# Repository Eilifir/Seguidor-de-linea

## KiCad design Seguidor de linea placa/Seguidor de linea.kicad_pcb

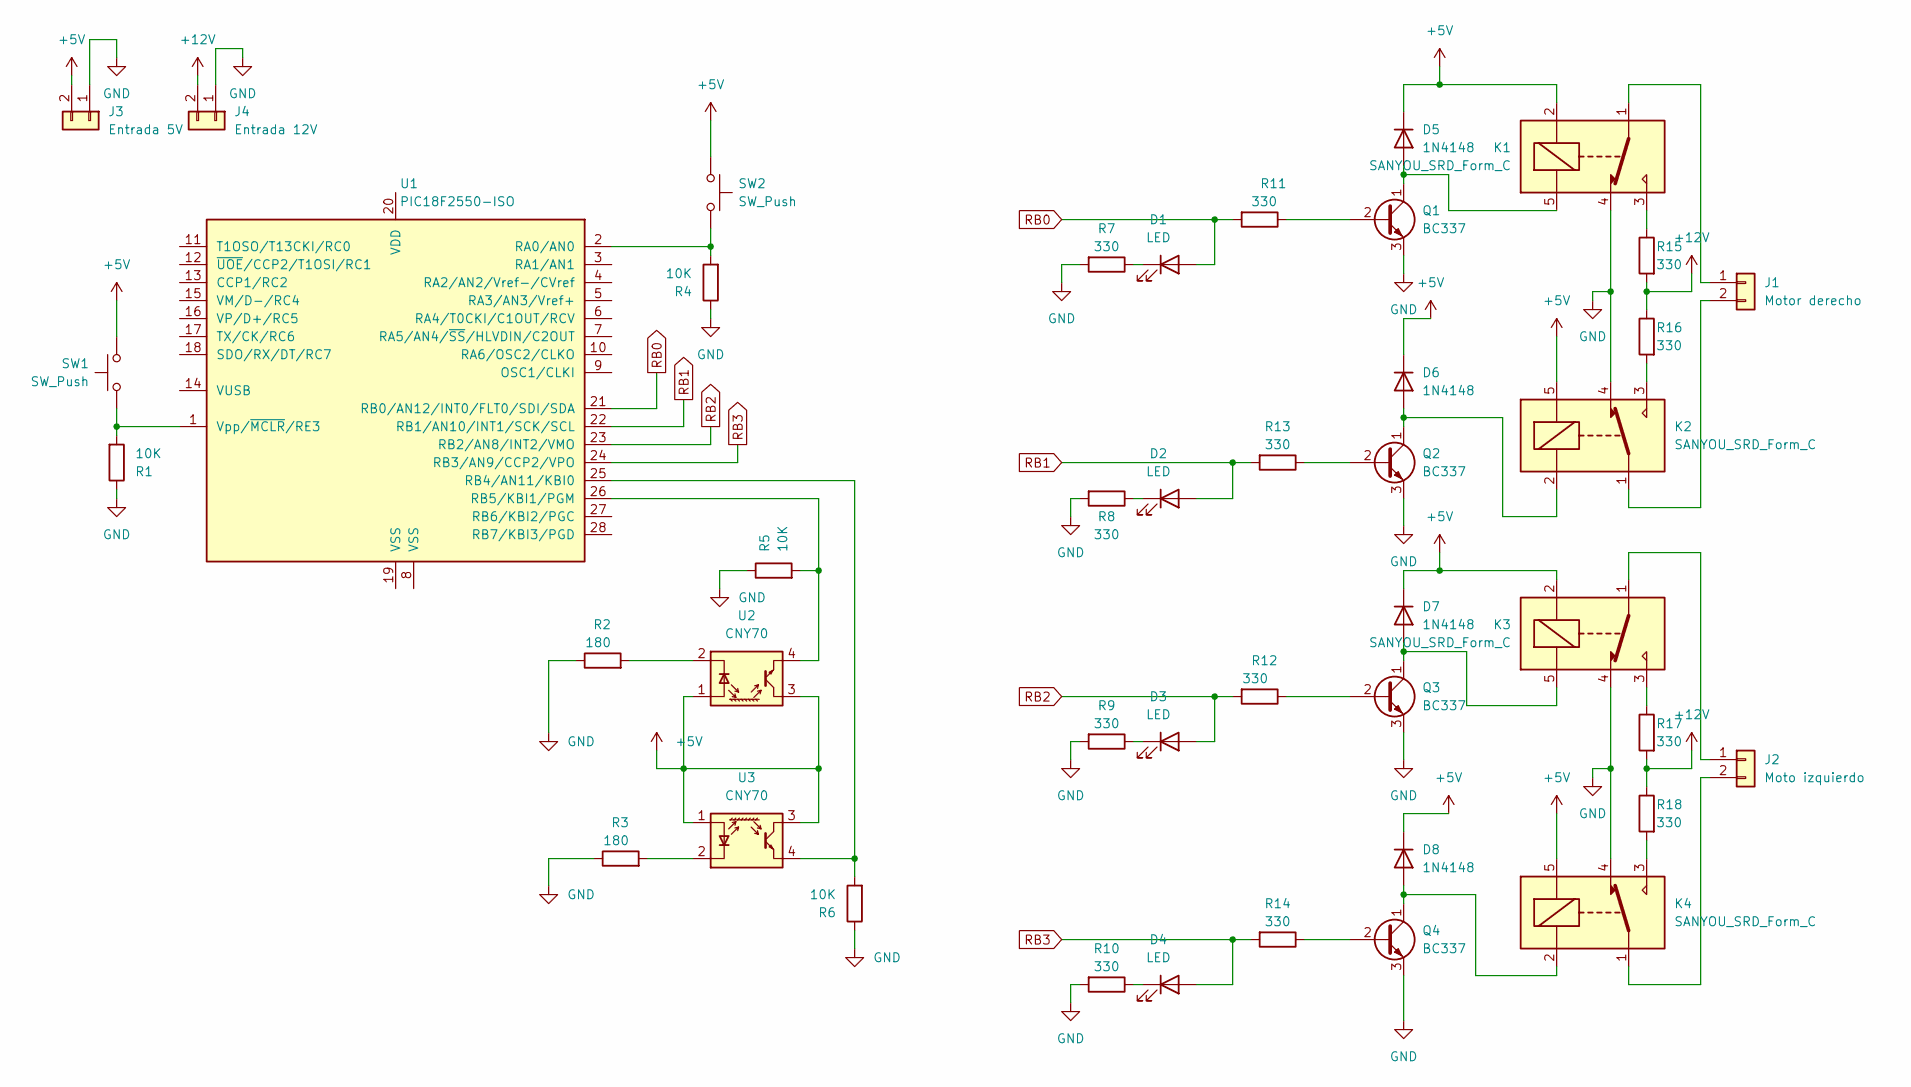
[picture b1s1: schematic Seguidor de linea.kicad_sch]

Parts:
D1, D2, D3, D4: LED; D_DO-35_SOD27_P7.62mm_Horizontal
D5, D6, D7, D8: 1N4148; D_DO-35_SOD27_P7.62mm_Horizontal
J1: Motor derecho; PhoenixContact_MSTBA_2,5_2-G_1x02_P5.00mm_Horizontal
J2: Moto izquierdo; PhoenixContact_MSTBA_2,5_2-G_1x02_P5.00mm_Horizontal
J3: Entrada 5V; PhoenixContact_MSTBA_2,5_2-G_1x02_P5.00mm_Horizontal
J4: Entrada 12V; PhoenixContact_MSTBA_2,5_2-G_1x02_P5.00mm_Horizontal
K1, K2, K3, K4: SANYOU_SRD_Form_C; Relay_SPDT_SANYOU_SRD_Series_Form_C
Q1, Q2, Q3, Q4: BC337; TO-92_Inline
R1, R4, R5, R6: 10K; R_Axial_DIN0207_L6.3mm_D2.5mm_P10.16mm_Horizontal
R2, R3: 180; R_Axial_DIN0207_L6.3mm_D2.5mm_P10.16mm_Horizontal
R7, R8, R9, R10, R11, R12, R13, R14, R15, R16, R17, R18: 330; R_Axial_DIN0207_L6.3mm_D2.5mm_P10.16mm_Horizontal
SW1, SW2: SW_Push; Molex_KK-396_A-41792-0002_1x02_P3.96mm_Horizontal
U1: PIC18F2550-ISO; DIP-28_W7.62mm_Socket_LongPads
U2, U3: CNY70; Vishay_CNY70

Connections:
+5V: D5.1 (K), D6.1 (K), D7.1 (K), D8.1 (K), J3.2, K1.2, K2.5, K3.2, K4.5, SW1.1, SW2.1, U2.1 (A), U2.3 (C), U3.1 (A), U3.3 (C)
+12V: J4.2, R15.2, R16.1, R17.2, R18.1
GND: J3.1, J4.1, K1.4, K2.4, K3.4, K4.4, Q1.3 (E), Q2.3 (E), Q3.3 (E), Q4.3 (E), R1.1, R2.1, R3.1, R4.1, R5.1, R6.1, R7.2, R8.2, R9.2, R10.2
unnamed: D1.1 (K), R7.1
unnamed: D2.1 (K), R8.1
unnamed: D3.1 (K), R9.1
unnamed: D4.1 (K), R10.1
unnamed: D5.2 (A), K1.5, Q1.1 (C)
unnamed: D6.2 (A), K2.2, Q2.1 (C)
unnamed: D7.2 (A), K3.5, Q3.1 (C)
unnamed: D8.2 (A), K4.2, Q4.1 (C)
unnamed: J1.1, K1.1
unnamed: J1.2, K2.1
unnamed: J2.1, K3.1
unnamed: J2.2, K4.1
unnamed: K1.3, R15.1
unnamed: K2.3, R16.2
unnamed: K3.3, R17.1
unnamed: K4.3, R18.2
unnamed: Q1.2 (B), R11.1
unnamed: Q2.2 (B), R13.1
unnamed: Q3.2 (B), R12.1
unnamed: Q4.2 (B), R14.1
unnamed: R1.2, SW1.2, U1.1 (Vpp/~MCLR/RE3)
unnamed: R2.2, U2.2 (K)
unnamed: R3.2, U3.2 (K)
unnamed: R4.2, SW2.2, U1.2 (RA0/AN0)
unnamed: R5.2, U1.26 (RB5/KBI1/PGM), U2.4 (E)
unnamed: R6.2, U1.25 (RB4/AN11/KBI0), U3.4 (E)
RB0: D1.2 (A), R11.2, U1.21 (RB0/AN12/INT0/FLT0/SDI/SDA)
RB1: D2.2 (A), R13.2, U1.22 (RB1/AN10/INT1/SCK/SCL)
RB2: D3.2 (A), R12.2, U1.23 (RB2/AN8/INT2/VMO)
RB3: D4.2 (A), R14.2, U1.24 (RB3/AN9/CCP2/VPO)

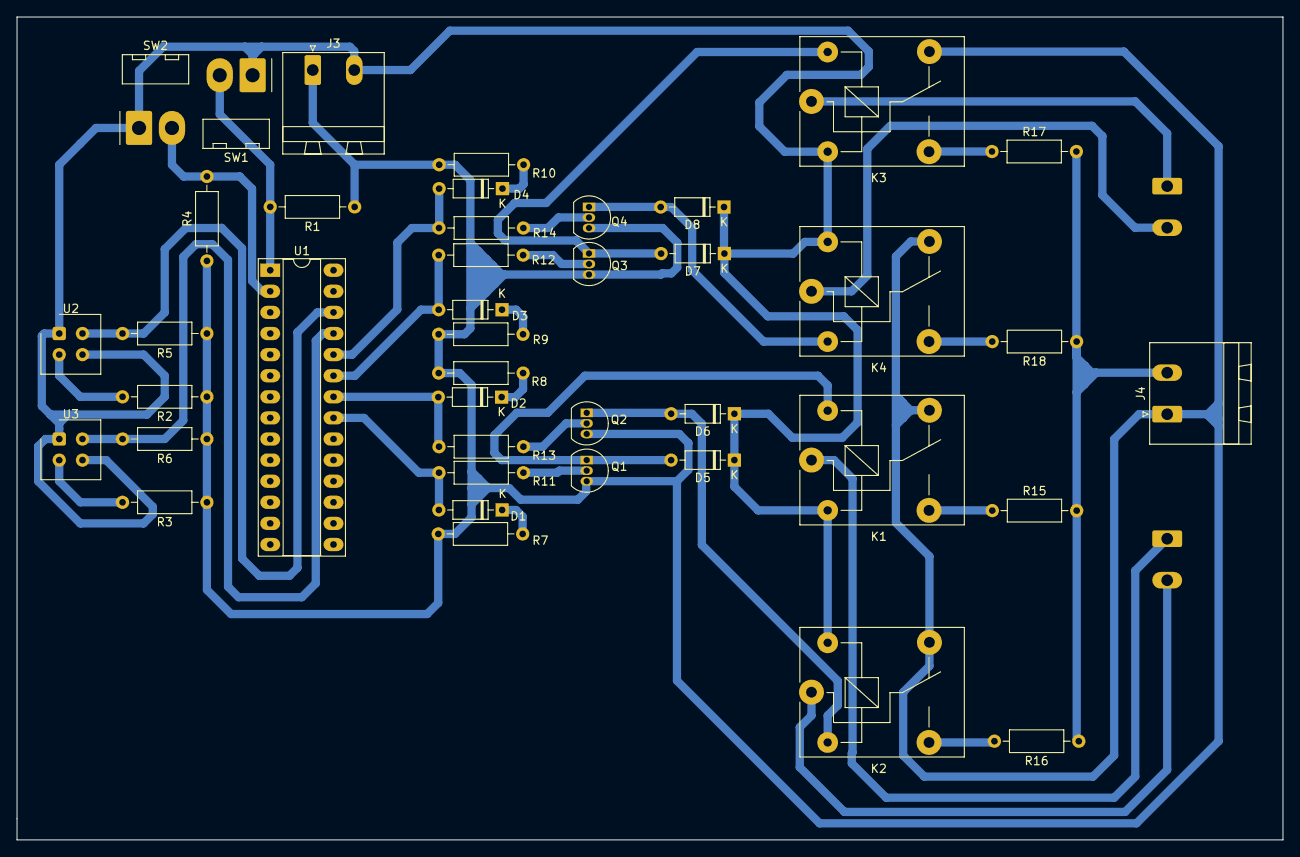
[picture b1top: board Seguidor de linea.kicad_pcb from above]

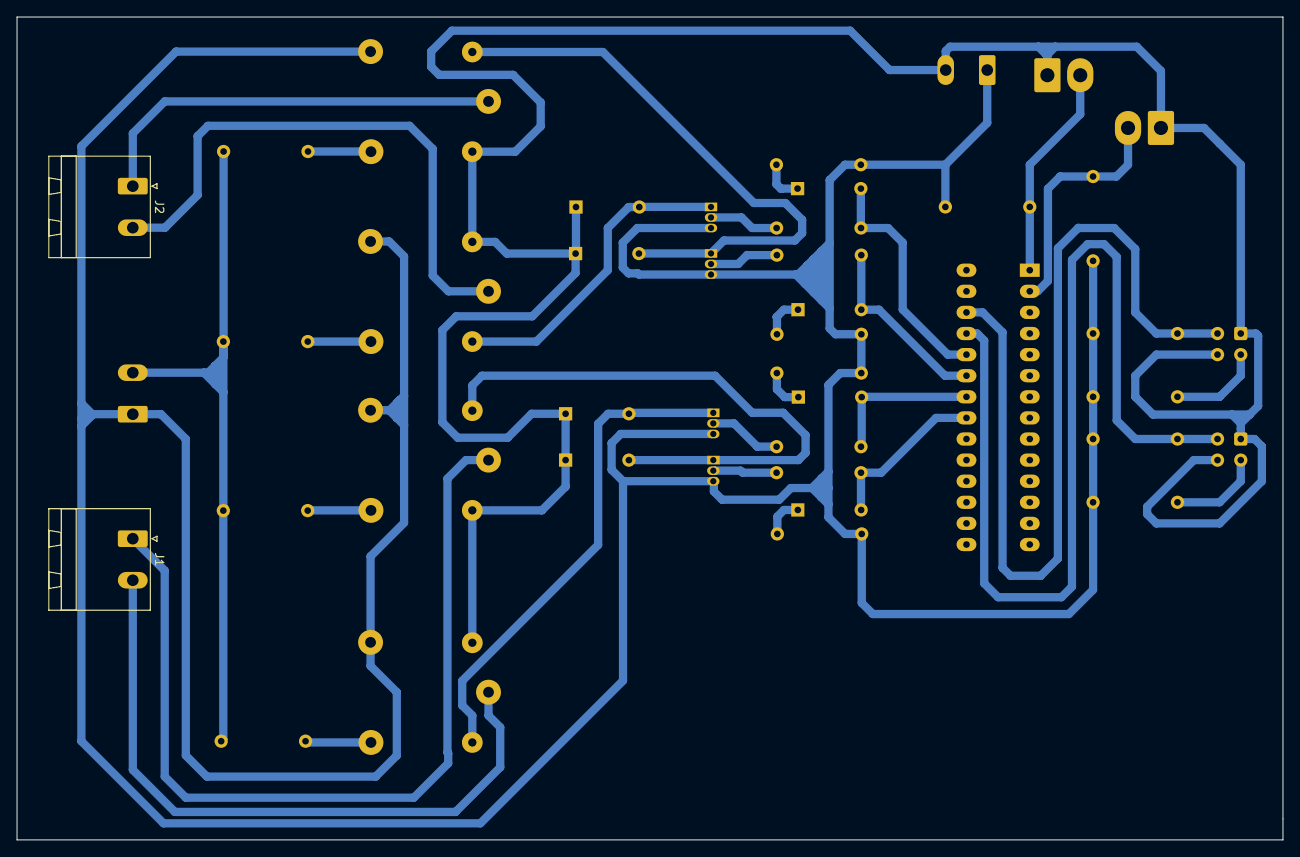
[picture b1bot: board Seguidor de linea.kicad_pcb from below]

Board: 2 copper layers, 152.4 x 99.1 mm, 43 parts (2 on the bottom side), 33 nets.
